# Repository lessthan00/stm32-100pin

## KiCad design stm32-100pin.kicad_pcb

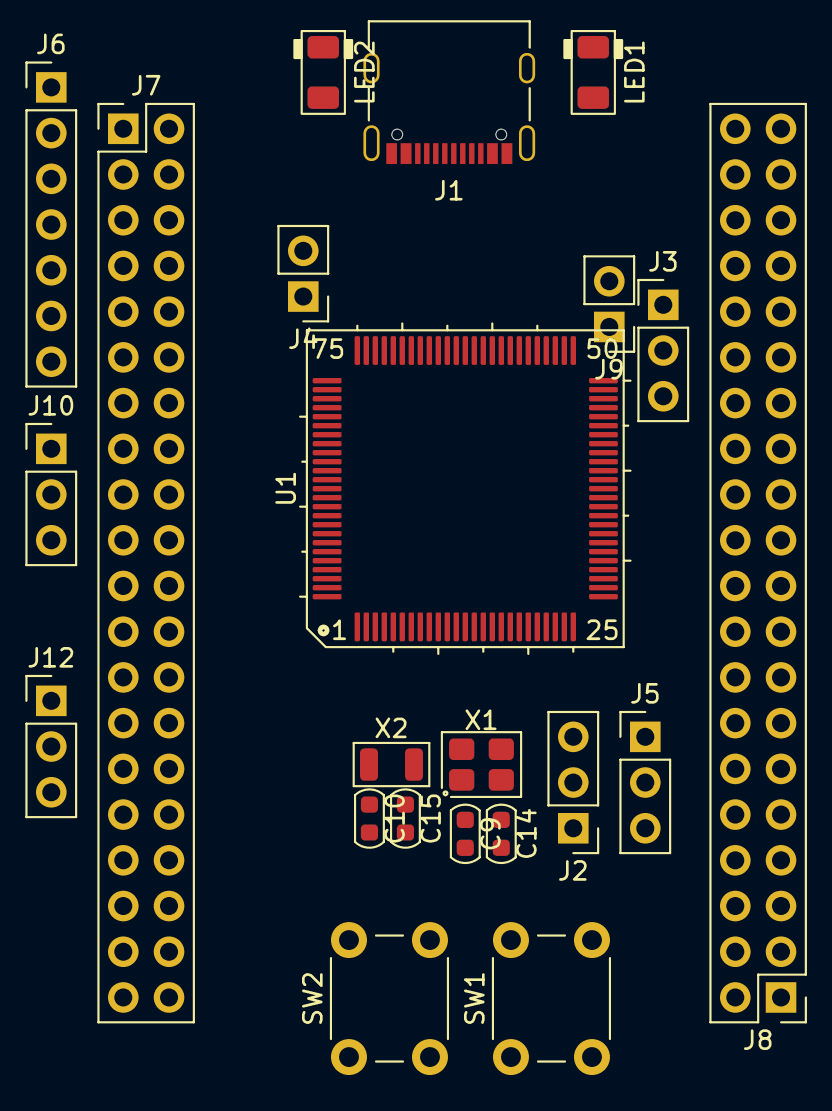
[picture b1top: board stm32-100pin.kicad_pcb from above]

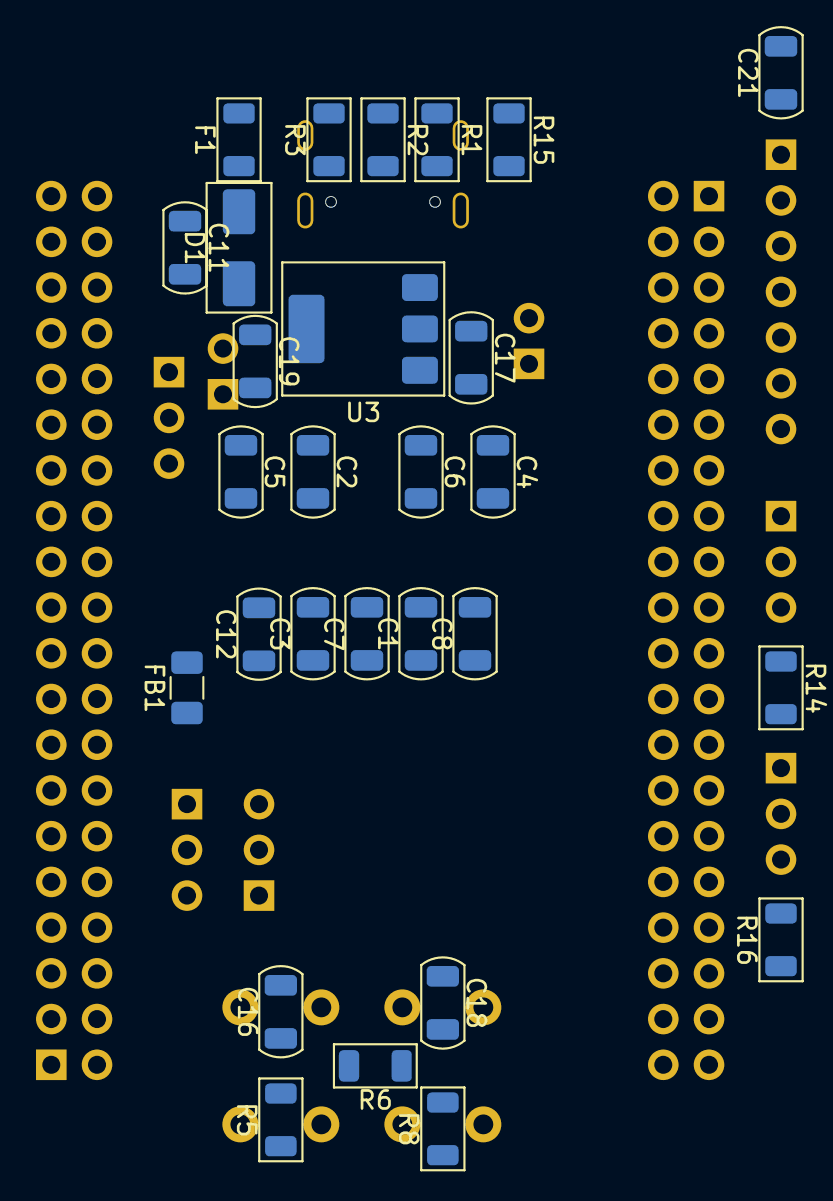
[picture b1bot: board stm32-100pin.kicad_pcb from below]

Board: 2 copper layers, 50 parts (28 on the bottom side), 104 nets, no tracks yet.

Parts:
C1, C3, C4, C5, C7, C8, C11, C12, C16, C18, C21: 100nF; C_1206_3216Metric
C2, C6: 2.2uF; C_1206_3216Metric
C9, C10, C14, C15: 22pF; C_0603_1608Metric
C17, C19: 10uF; C_1206_3216Metric
D1: SMAJ6.5CA; D_SMA_TVS
F1: 5V1A; R_1206_3216Metric
FB1: FerriteBead; R_1206_3216Metric
J1: USB_C_Receptacle_USB2.0_16P; USB_C_Receptacle_Palconn_UTC16-G
J2, J3, J5, J10, J12: Conn_01x03; PinHeader_1x03_P2.54mm_Vertical
J4, J9: Conn_01x02; PinHeader_1x02_P2.54mm_Vertical
J6: PINHD_1x7_Male; PinHeader_1x07_P2.54mm_Vertical
J7, J8: Conn_02x20_Odd_Even; PinHeader_2x20_P2.54mm_Vertical
LED1: LED_1206; LED_1206_3216Metric
LED2: 红; LED_1206_3216Metric
R1: 1.5KΩ; R_1206_3216Metric
R2, R3: 5.1KΩ; R_1206_3216Metric
R5, R6, R8, R14, R15, R16: 10KΩ; R_1206_3216Metric
SW1, SW2: SW_Push; SW_PUSH_6mm_H7.3mm
U1: STM32F103VETx; LQFP-100_14x14mm_P0.5mm
U3: AZ1117IH-3.3TRE1; SOT-223-3_TabPin2
X1: SMD3225-4; Crystal_SMD_3225-4Pin_3.2x2.5mm
X2: SMD3215-2; Crystal_SMD_3215-2Pin_3.2x1.5mm

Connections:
+3.3V: C3.1, C4.1, C5.1, C7.1, C8.1, C18.1, C21.1, J2.1, J5.3, J6.1, J9.1, J10.1, J12.3, R1.1, R5.1, R15.1, SW2.2, U1.11 (VDD), U1.21 (VREF+), U1.28 (VDD), U1.50 (VDD), U1.75 (VDD), U1.100 (VDD)
+5V: C17.1, U3.3 (IN)
+BATT: C1.1, J7.30, U1.6 (VBAT)
/BOOT0: R14.2, U1.94 (BOOT0)
/JTCK-SWCLK: J6.3, U1.76 (PA14)
/JTDI: J6.6, U1.77 (PA15)
/JTDO: J6.7, U1.89 (PB3)
/JTMS-SWDIO: J6.2, U1.72 (PA13)
/NRST: C16.1, J6.5, J7.34, R5.2, SW1.2, U1.14 (NRST)
/OSC+: C9.1, U1.12 (OSC_IN), X1.1
/OSC-: C14.1, U1.13 (OSC_OUT), X1.3
/PA0: J7.37, U1.23 (PA0)
/PA1: J7.40, U1.24 (PA1)
/PA2: J7.39, U1.25 (PA2)
/PA3: J8.2, U1.26 (PA3)
/PA4: J8.1, U1.29 (PA4)
/PA5: J8.4, U1.30 (PA5)
/PA6: J8.3, U1.31 (PA6)
/PA7: J8.6, U1.32 (PA7)
/PA8: J8.37, U1.67 (PA8)
/PA9: J8.40, U1.68 (PA9)
/PA10: J8.39, U1.69 (PA10)
/PB0: J8.7, U1.35 (PB0)
/PB1: J8.10, U1.36 (PB1)
/PB2: J8.9, U1.37 (PB2)
/PB4: J7.15, U1.90 (PB4)
/PB5: J7.18, U1.91 (PB5)
/PB6: J7.17, U1.92 (PB6)
/PB7: J7.20, U1.93 (PB7)
/PB8: J7.19, U1.95 (PB8)
/PB9: J7.22, U1.96 (PB9)
/PB10: J8.19, U1.47 (PB10)
/PB11: J8.22, U1.48 (PB11)
/PB12: J8.21, U1.51 (PB12)
/PB13: J8.24, U1.52 (PB13)
/PB14: J8.23, U1.53 (PB14)
/PB15: J8.26, U1.54 (PB15)
/PC0: J7.33, U1.15 (PC0)
/PC1: J7.36, U1.16 (PC1)
/PC2: J7.35, U1.17 (PC2)
/PC3: J7.38, U1.18 (PC3)
/PC4: J8.5, U1.33 (PC4)
/PC5: J8.8, U1.34 (PC5)
/PC6: J8.33, U1.63 (PC6)
/PC7: J8.36, U1.64 (PC7)
/PC8: J8.35, U1.65 (PC8)
/PC9: J8.38, U1.66 (PC9)
/PC10: J7.3, U1.78 (PC10)
/PC11: J7.6, U1.79 (PC11)
/PC12: J7.5, U1.80 (PC12)
/PC13: J7.29, U1.7 (PC13)
/PC14: C10.1, J7.32, U1.8 (PC14), X2.2
/PC15: C15.1, J7.31, U1.9 (PC15), X2.1
/PD0: J7.8, U1.81 (PD0)
/PD1: J7.7, U1.82 (PD1)
/PD2: J7.10, U1.83 (PD2)
/PD3: J7.9, U1.84 (PD3)
/PD4: J7.12, U1.85 (PD4)
/PD5: J7.11, U1.86 (PD5)
/PD6: J7.14, U1.87 (PD6)
/PD7: J7.13, U1.88 (PD7)
/PD8: J8.25, U1.55 (PD8)
/PD9: J8.28, U1.56 (PD9)
/PD10: J8.27, U1.57 (PD10)
/PD11: J8.30, U1.58 (PD11)
/PD12: J8.29, U1.59 (PD12)
/PD13: J8.32, U1.60 (PD13)
/PD14: J8.31, U1.61 (PD14)
/PD15: J8.34, U1.62 (PD15)
/PE0: J7.21, U1.97 (PE0)
/PE1: J7.24, U1.98 (PE1)
/PE2: J7.23, U1.1 (PE2)
/PE3: J7.26, U1.2 (PE3)
/PE4: J7.25, U1.3 (PE4)
/PE5: J7.28, U1.4 (PE5)
/PE6: J7.27, U1.5 (PE6)
/PE7: J8.12, U1.38 (PE7)
/PE8: J8.11, U1.39 (PE8)
/PE9: J8.14, U1.40 (PE9)
/PE10: J8.13, U1.41 (PE10)
/PE11: J8.16, U1.42 (PE11)
/PE12: J8.15, U1.43 (PE12)
/PE13: J8.18, U1.44 (PE13)
/PE14: J8.17, U1.45 (PE14)
/PE15: J8.20, U1.46 (PE15)
/PIN3_3V: C19.1, J9.2, U3.2 (OUT)
/USBDM: J1.A7 (D-), J1.B7 (D-)
/USBDP: J1.A6 (D+), J1.B6 (D+), R1.2
GND: C1.2, C2.2, C3.2, C4.2, C5.2, C6.2, C7.2, C8.2, C9.2, C10.2, C11.2, C12.2, C14.2, C15.2, C16.2, C17.2, C19.2, C21.2, D1.1 (K), J1.A1 (GND), J1.A12 (GND), J1.B1 (GND), J1.B12 (GND), J1.S1 (SHIELD), J2.3, J3.1, J6.4, J10.3, J12.1, LED1.1 (K), LED2.1 (K), R2.1, R3.2, R6.2, SW1.1, U1.10 (VSS), U1.20 (VREF-), U1.27 (VSS), U1.74 (VSS), U1.99 (VSS), U3.1, X1.2, X1.4
unnamed: C18.2, R6.1, R8.2, SW2.1
unnamed: F1.2, J1.A4 (VBUS), J1.A9 (VBUS), J1.B4 (VBUS), J1.B9 (VBUS)
unnamed: J1.A5 (CC1), R3.1
unnamed: J1.B5 (CC2), R2.2
unnamed: J2.2, U1.19 (VSSA)
unnamed: J3.2, U1.49 (VSS)
unnamed: C2.1, J3.3
unnamed: J4.1, U1.73 (NC)
unnamed: C6.1, J4.2
unnamed: FB1.1, J5.2
unnamed: J10.2, R14.1
unnamed: J12.2, R16.2
unnamed: LED2.2 (A), R15.2
VBUS: C11.1, D1.2 (A), F1.1, LED1.2 (A)
VDDA: C12.1, FB1.2, U1.22 (VDDA)
